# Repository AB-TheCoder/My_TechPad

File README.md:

# My_TechPad

- My OWN custom Macropad.

---

# Dream:

- What i plan , is to make a esthetic and slick hackpad which will have a the following features:
  1. The hackpad will have rgb lightning and will be connected to a device using wired connection(usb)
  2. it will have its own application which will allow to set commands and actions for the button
  3. it will be aesthetic black in colour with crazy lighting (customizable through app)
  4. i am planning to keep it simple and in devoloper theme.
  5. it will be a slick and esthetic desing, with 2 rotatory encoder, a oled screen , 12 keypads
  6. i dont plan on using anything extra or of my own .
  7. good animations for oled is also a requisite.
  8. as for the design i am planning , something of a
     - minimalist , slick , futuristc look
     - 3d printed mat finish
     - a usb port to connected to devices.

# desgin :

- I think my design is quite close to the image i had in my head.

1. it is slick and has a simplistic look.
2. black colour frame with rgb colouring.
3. Smooth finish
4. What more does a man need!!

# Screenshots:

- the whole thing put together:

- the schematic:

- the PCB:

# Specifications:

- I am planning to use all the items i will get under hackpad.

1. my hackpad will have 12 keys along with a rotary encoder knob.
   - 12 MX switches in a 4 x 3 grid, with white DSA keycaps.
   - 1 EC11 knob that you can also click. (the dream had 2 knobs, but i ran out of pins so one had to go. rip.)
2. the brain is a Seeed XIAO RP2040, plugged in with USB-C.
3. a tiny 0.91" OLED screen (128 x 32) on the top left. it shows which mode you're in, your typing speed (WPM) and the TechPad logo.
4. 12 RGB LEDs (SK6812 MINI-E), one under every key. they glow when you press a key and then fade out.
   - brightness is capped at 40%, because 12 LEDs at full blast would pull ~720 mA and USB only gives 500 mA. at 40% it's about 290 mA, so we're safe.
5. the XIAO only has 11 pins, so i couldn't wire the keys the normal way. i used a **duplex matrix** instead: 6 pins + 13 diodes read all 12 keys AND the knob click. no extra chips needed.
6. the PCB is 92 x 87 mm, 2 layers, with ground fill on both sides. 0 ERC errors and 0 DRC errors in KiCad.
7. the case is 3D printed in charcoal, in 3 pieces (bottom tray, switch plate, top frame). it's 98 x 93 x 22.4 mm, and the screws go in from the bottom so you don't see any on top.

# Firmware:

- built on QMK, but the key scanner (`matrix.c`) is all mine. it scans the matrix twice, once for each diode direction.

1. 3 modes: DEVELOPER, MEDIA and RGB.
2. click the knob to jump to the next mode.
3. turn the knob for volume (or LED brightness in RGB mode).
4. DEVELOPER mode has copy, paste, cut, undo, save, find, comment, VS Code commands, terminal, alt+tab, lock PC and mute.
5. MEDIA mode has play/pause, next and previous track, volume, screen brightness, calculator, browser and files.
6. RGB mode lets you switch the lights on/off, change effects, colour, brightness and speed.

- this modes are just a few basic things i am adding for now. in future i am planning to create my app to allow the user to customize the shortcuts and make his/hers own layers.The app can also be used to customize rgb and animations.lets hope all works out.....

# BOM:

- everything comes from the hackpad kit, except the PCB (made from my gerbers) and the 3D printed case. full list is in [Documentation/BOM.csv](Documentation/BOM.csv).

| Ref | Part | Qty | Where | Source |
|---|---|---|---|---|
| U1 | Seeed XIAO RP2040 (through-hole mount) | 1 | Back of PCB | Hackpad kit |
| SW1 to SW12 | MX-style mechanical switch | 12 | Top plate + PCB | Hackpad kit |
| - | White blank DSA keycap | 12 | On the switches | Hackpad kit |
| SW13 | EC11E rotary encoder with push switch | 1 | Top right | Hackpad kit |
| D1 to D13 | 1N4148 diode, DO-35 through-hole | 13 | Next to each switch | Hackpad kit |
| LED1 to LED12 | SK6812 MINI-E RGB LED (reverse mount) | 12 | Under each key | Hackpad kit |
| J1 + display | 0.91" I²C OLED module, 4-pin header | 1 | Top left | Hackpad kit |
| - | M3 × 16 mm screw | 4 | From underneath, through PCB corners | Hackpad kit |
| - | M3 × 5 × 4 mm heat-set insert | 4 | Underside of the top frame, at the corners | Hackpad kit |
| - | TechPad PCB, 92 × 87 mm, 2-layer | 1 | - | PCB fab (from gerbers.zip) |
| - | Top frame, switch plate, bottom tray, knob cap | 1 set | - | 3D printed |

# "How to build" A numbered list covering:

- Print: frame face-down, plate top-face-down with solid infill, tray floor-down, knob hole-side down. No supports.
- Heat-set inserts: 4 × M3 into the underside of the frame.
- Solder order: diodes (black stripe matches the silkscreen), XIAO on the back, LEDs, switches, encoder, then the - OLED raised about 3.5 mm on its pins.
- Assembly: stack tray, PCB, plate, frame, then fit 4 × M3×16 screws from underneath and push on the knob.
- Flash: hold the top-left key (or the XIAO BOOT button) while plugging in, then drag Production/firmware.uf2 onto the RPI-RP2 drive.
- Link Documentation/reference/05_After_Parts_Arrive.pdf for full details.

# Disclosure:
- Ai has Played a important part in the project for me. I have never designed pcb,step files or used QMK before this and Ai has acted as my gude solving this challanges.This section Provides a complete discloure of the places where ai has played a part:
1. To create the final design/product outlook upon which i have build my entire project.It is very important that one knows what one wants in the end. i have used ai to help me get a final image of the pad.
2. I have asked Ai to create me guides and explanation pdfs for every bit of project(can be found under documentation).This guides has helped me understand the stuff i was working on .
3.The schematic designs is all done by me , the footprints and all stuff. I have only asked claude to regularly review my files and do  the final routing . i had already created the schematic and had to just join the wires.
4. In Case Design , i have used claude ai to create me the drawings upon which i have created the designs.Claude has also helped me create steps file by providing me with macros code.(it was very labour intensive and repeatative work so ya)
5. i can vouch for my 100% role in firmware devolpment. Claude has only acted as a mentor , and i have typed every peice of code.
6. lastly i have used claude to review my files so that they match each other and are not incomplete anywhere.

# Final Thanks and feedback:
-   I thank the enitre team of hackclub for organising such cool and wonderfull programs and allowing teens to bring there work on action. With this project i have learnt a lot and am planning to work on more projects as well.
- One thing i think you guys lack on is the clarity you guys are providing . like ,there are many times i have not recieved a proper reply which has left me confused .

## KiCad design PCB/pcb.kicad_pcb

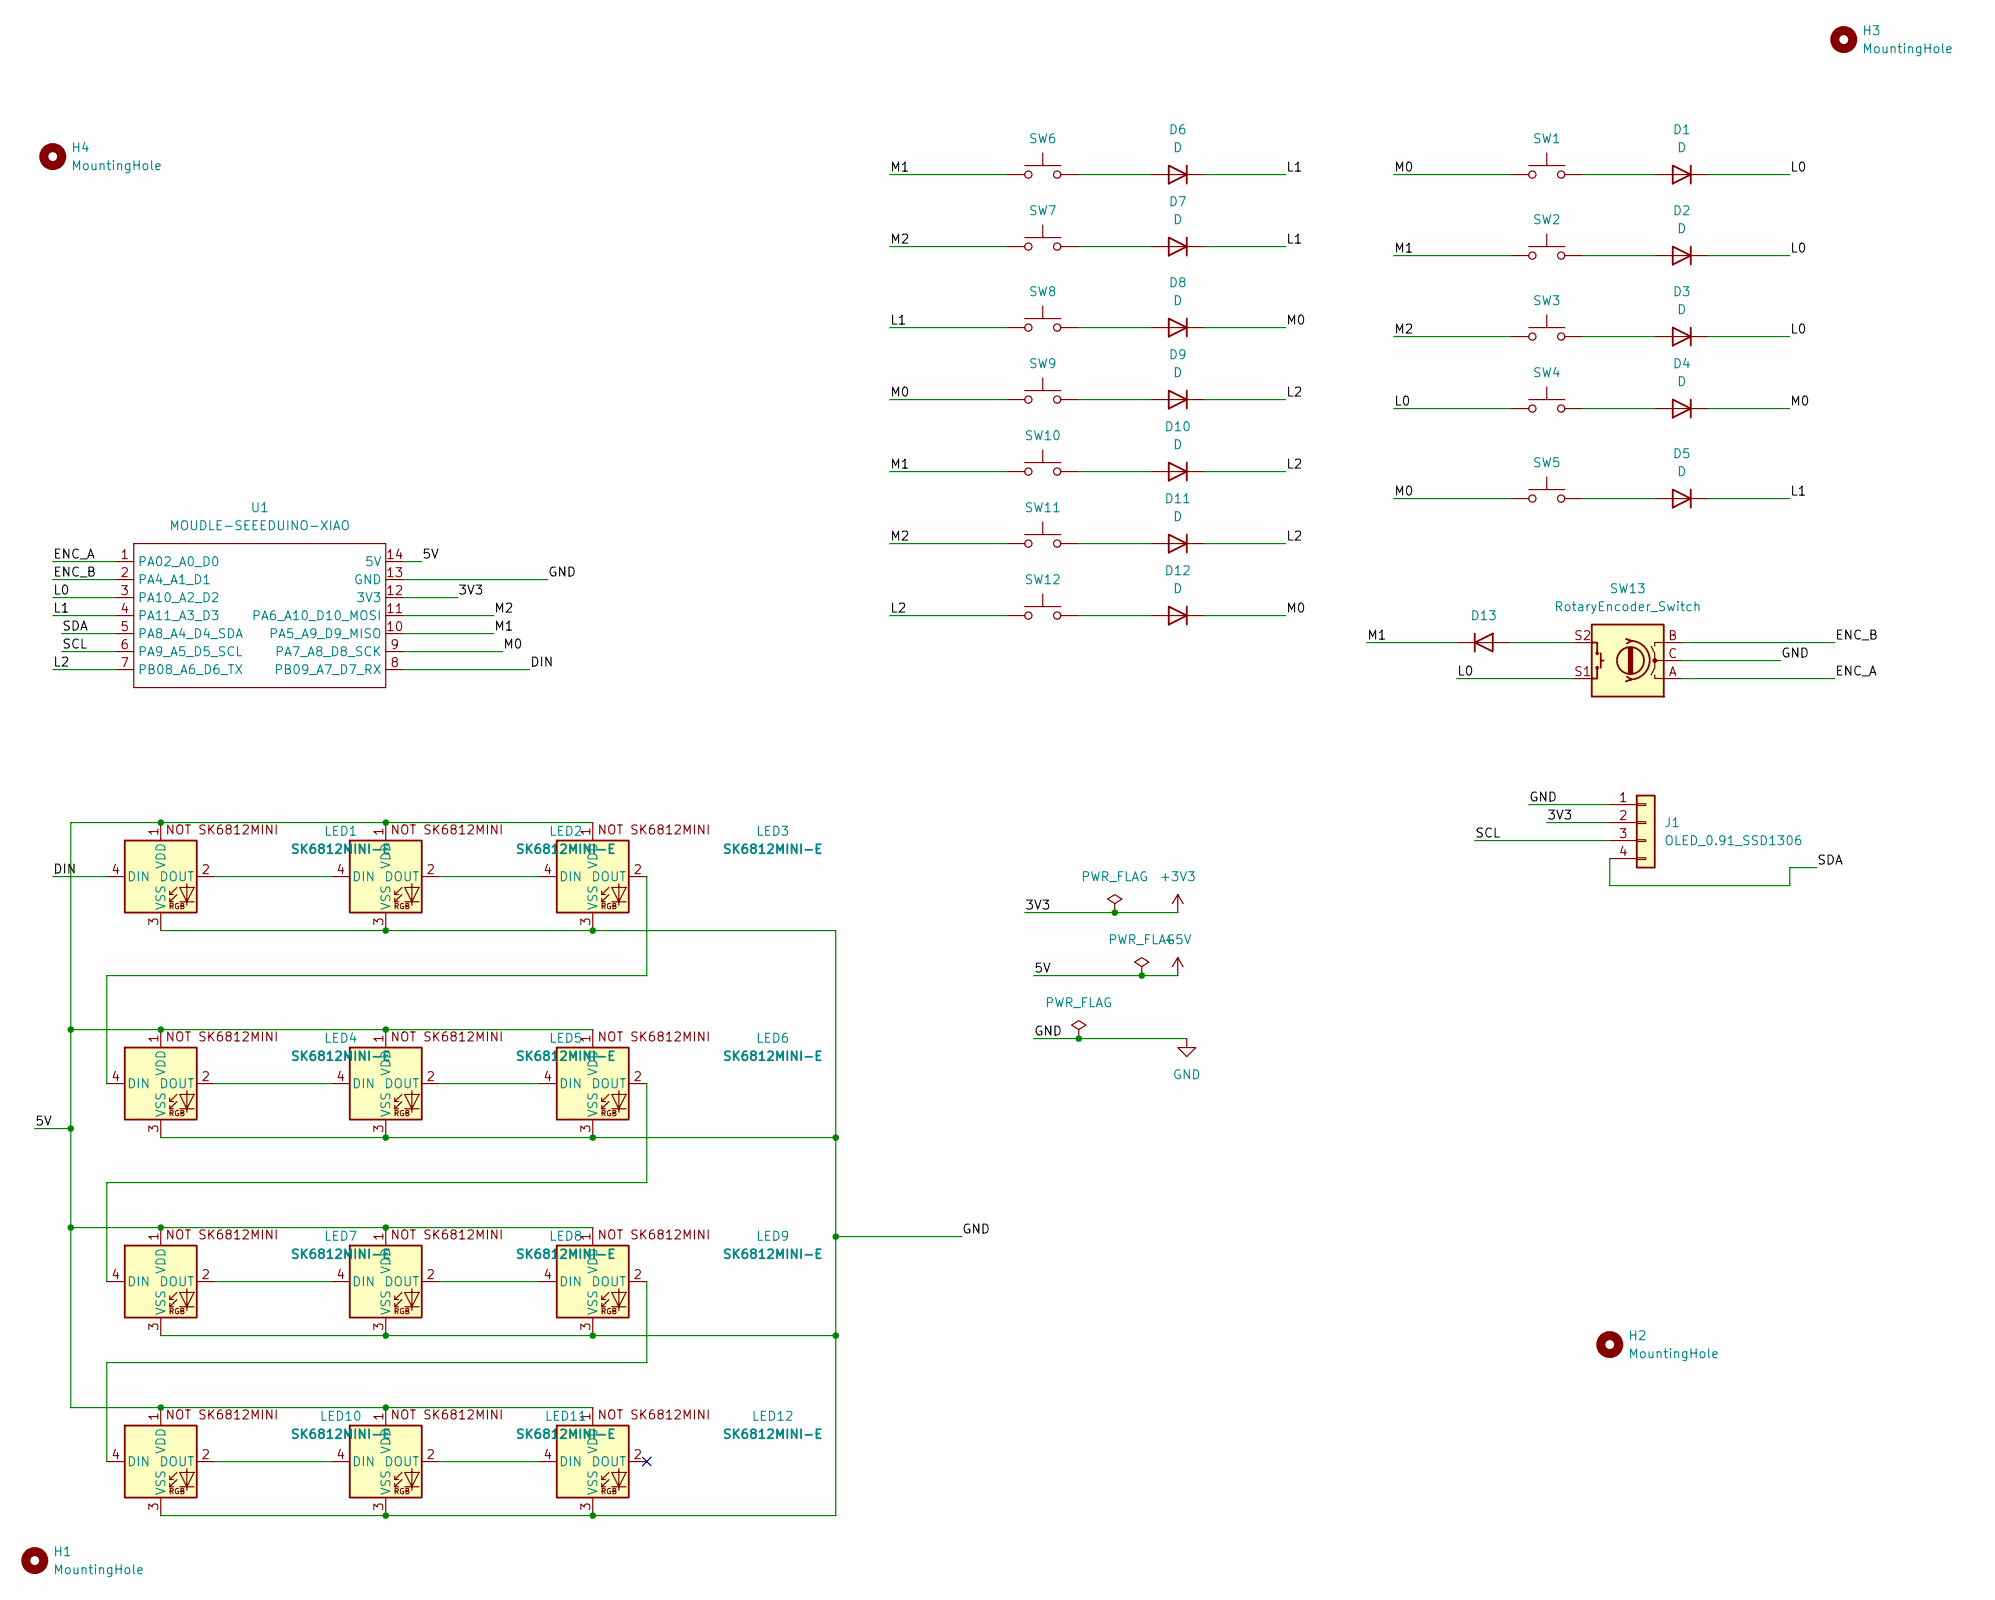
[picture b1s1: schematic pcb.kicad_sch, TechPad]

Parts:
D1, D2, D3, D4, D5, D6, D7, D8, D9, D10, D11, D12, D13: D; D_DO-35_SOD27_P7.62mm_Horizontal
H1, H2, H3, H4: MountingHole; MountingHole_3.2mm_M3
J1: OLED_0.91_SSD1306; PinHeader_1x04_P2.54mm_Vertical
LED1, LED2, LED3, LED4, LED5, LED6, LED7, LED8, LED9, LED10, LED11, LED12: SK6812MINI-E; SK6812MINI-E_fixed
SW1, SW2, SW3, SW4, SW5, SW6, SW7, SW8, SW9, SW10, SW11, SW12: SW_Push; SW_Cherry_MX_1.00u_PCB
SW13: RotaryEncoder_Switch; RotaryEncoder_Alps_EC11E-Switch_Vertical_H20mm
U1: MOUDLE-SEEEDUINO-XIAO; XIAO-Generic-Hybrid-14P-2.54-21X17.8MM

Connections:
+3V3: J1.2, U1.12 (3V3)
+5V: LED1.1 (VDD), LED2.1 (VDD), LED3.1 (VDD), LED4.1 (VDD), LED5.1 (VDD), LED6.1 (VDD), LED7.1 (VDD), LED8.1 (VDD), LED9.1 (VDD), LED10.1 (VDD), LED11.1 (VDD), LED12.1 (VDD), U1.14 (5V)
/DIN: LED1.4 (DIN), U1.8 (PB09_A7_D7_RX)
/ENC_A: SW13.A, U1.1 (PA02_A0_D0)
/ENC_B: SW13.B, U1.2 (PA4_A1_D1)
/L0: D1.1 (K), D2.1 (K), D3.1 (K), SW4.1, SW13.S1, U1.3 (PA10_A2_D2)
/L1: D5.1 (K), D6.1 (K), D7.1 (K), SW8.1, U1.4 (PA11_A3_D3)
/L2: D9.1 (K), D10.1 (K), D11.1 (K), SW12.1, U1.7 (PB08_A6_D6_TX)
/M0: D4.1 (K), D8.1 (K), D12.1 (K), SW1.1, SW5.1, SW9.1, U1.9 (PA7_A8_D8_SCK)
/M1: D13.1 (K), SW2.1, SW6.1, SW10.1, U1.10 (PA5_A9_D9_MISO)
/M2: SW3.1, SW7.1, SW11.1, U1.11 (PA6_A10_D10_MOSI)
/SCL: J1.3, U1.6 (PA9_A5_D5_SCL)
/SDA: J1.4, U1.5 (PA8_A4_D4_SDA)
GND: J1.1, LED1.3 (VSS), LED2.3 (VSS), LED3.3 (VSS), LED4.3 (VSS), LED5.3 (VSS), LED6.3 (VSS), LED7.3 (VSS), LED8.3 (VSS), LED9.3 (VSS), LED10.3 (VSS), LED11.3 (VSS), LED12.3 (VSS), SW13.C, U1.13 (GND)
unnamed: D1.2 (A), SW1.2
unnamed: D2.2 (A), SW2.2
unnamed: D3.2 (A), SW3.2
unnamed: D4.2 (A), SW4.2
unnamed: D5.2 (A), SW5.2
unnamed: D6.2 (A), SW6.2
unnamed: D7.2 (A), SW7.2
unnamed: D8.2 (A), SW8.2
unnamed: D9.2 (A), SW9.2
unnamed: D10.2 (A), SW10.2
unnamed: D11.2 (A), SW11.2
unnamed: D12.2 (A), SW12.2
unnamed: D13.2 (A), SW13.S2
unnamed: LED1.2 (DOUT), LED2.4 (DIN)
unnamed: LED2.2 (DOUT), LED3.4 (DIN)
unnamed: LED3.2 (DOUT), LED4.4 (DIN)
unnamed: LED4.2 (DOUT), LED5.4 (DIN)
unnamed: LED5.2 (DOUT), LED6.4 (DIN)
unnamed: LED6.2 (DOUT), LED7.4 (DIN)
unnamed: LED7.2 (DOUT), LED8.4 (DIN)
unnamed: LED8.2 (DOUT), LED9.4 (DIN)
unnamed: LED9.2 (DOUT), LED10.4 (DIN)
unnamed: LED10.2 (DOUT), LED11.4 (DIN)
unnamed: LED11.2 (DOUT), LED12.4 (DIN)

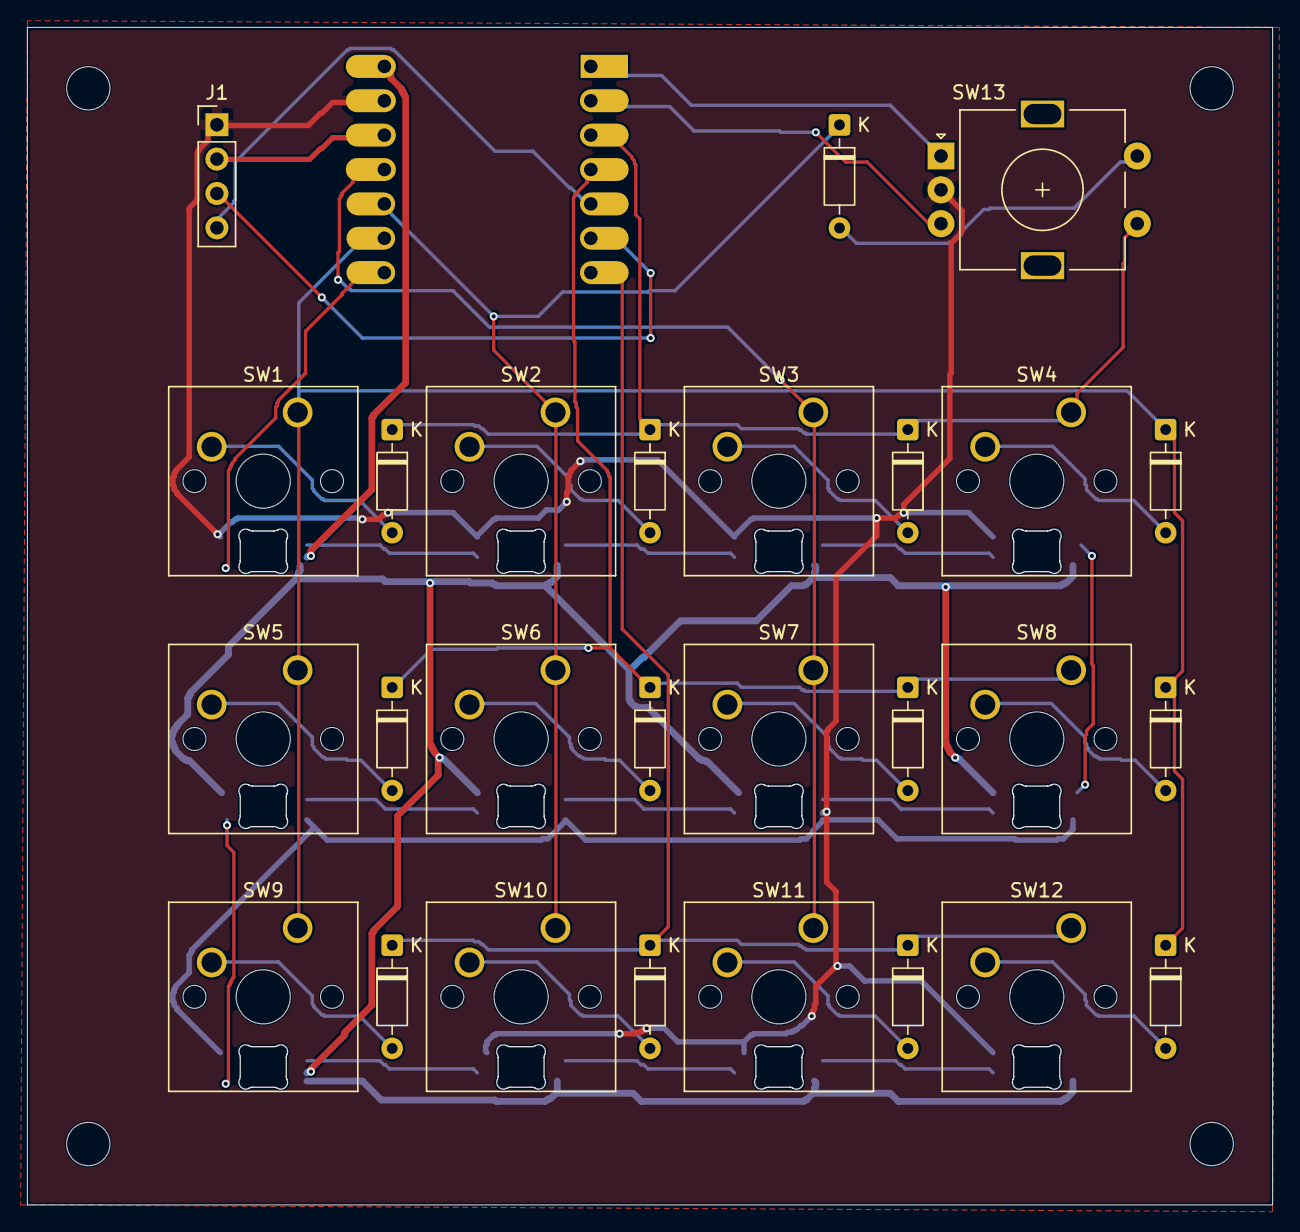
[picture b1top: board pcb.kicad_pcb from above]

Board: 2 copper layers, 92.0 x 87.0 mm, 44 parts (1 on the bottom side), 38 nets.
